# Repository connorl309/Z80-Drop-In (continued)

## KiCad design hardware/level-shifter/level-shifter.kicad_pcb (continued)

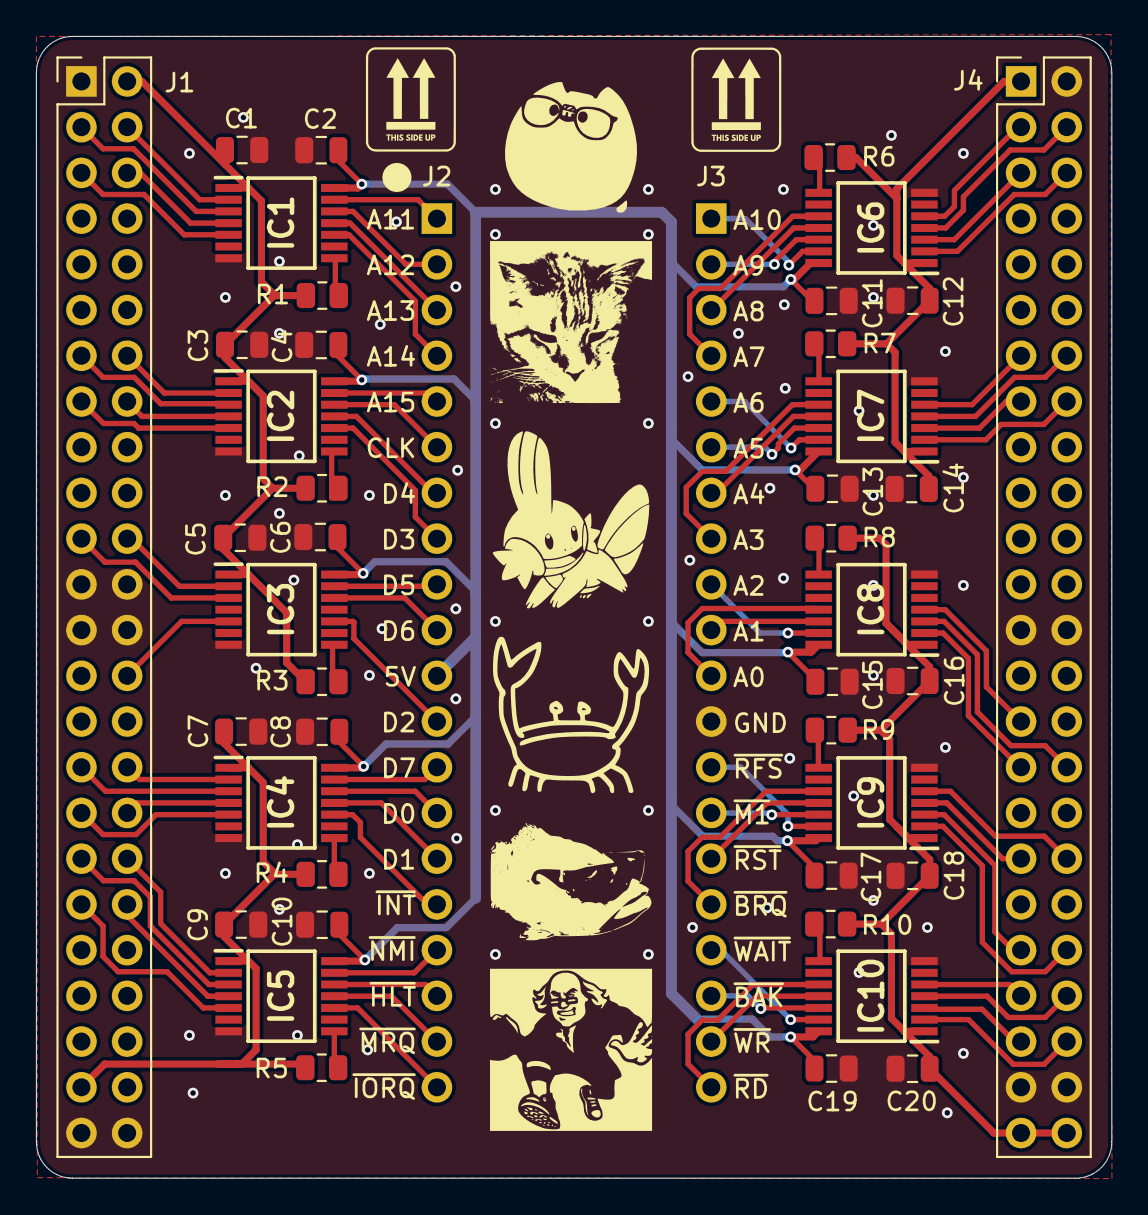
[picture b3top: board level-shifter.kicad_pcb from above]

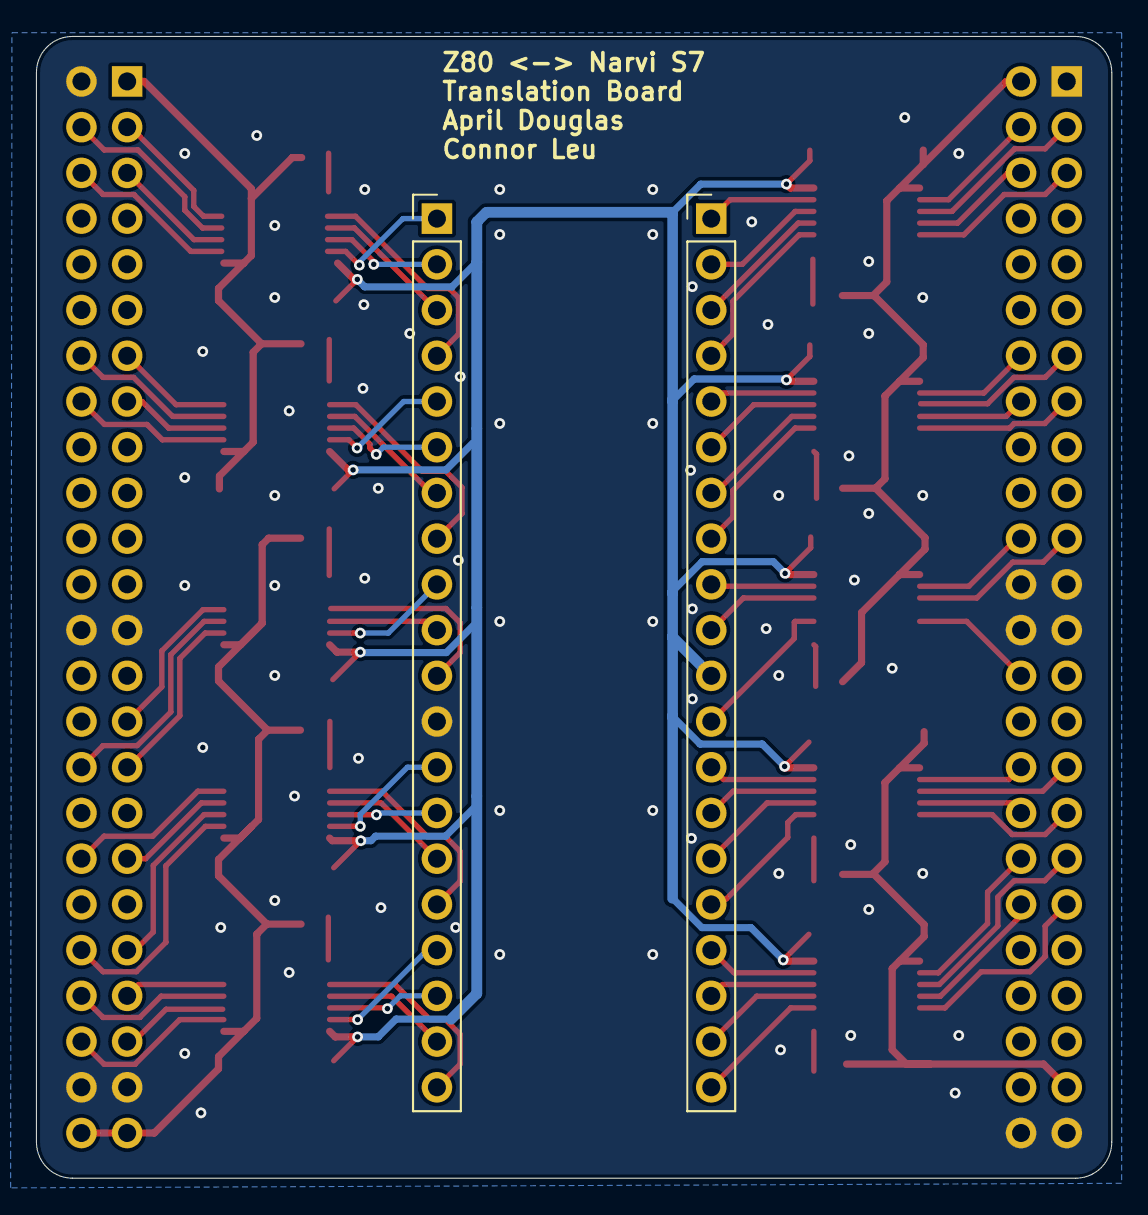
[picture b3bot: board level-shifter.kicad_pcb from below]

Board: 2 copper layers, 59.7 x 63.4 mm, 44 parts (2 on the bottom side), 92 nets.

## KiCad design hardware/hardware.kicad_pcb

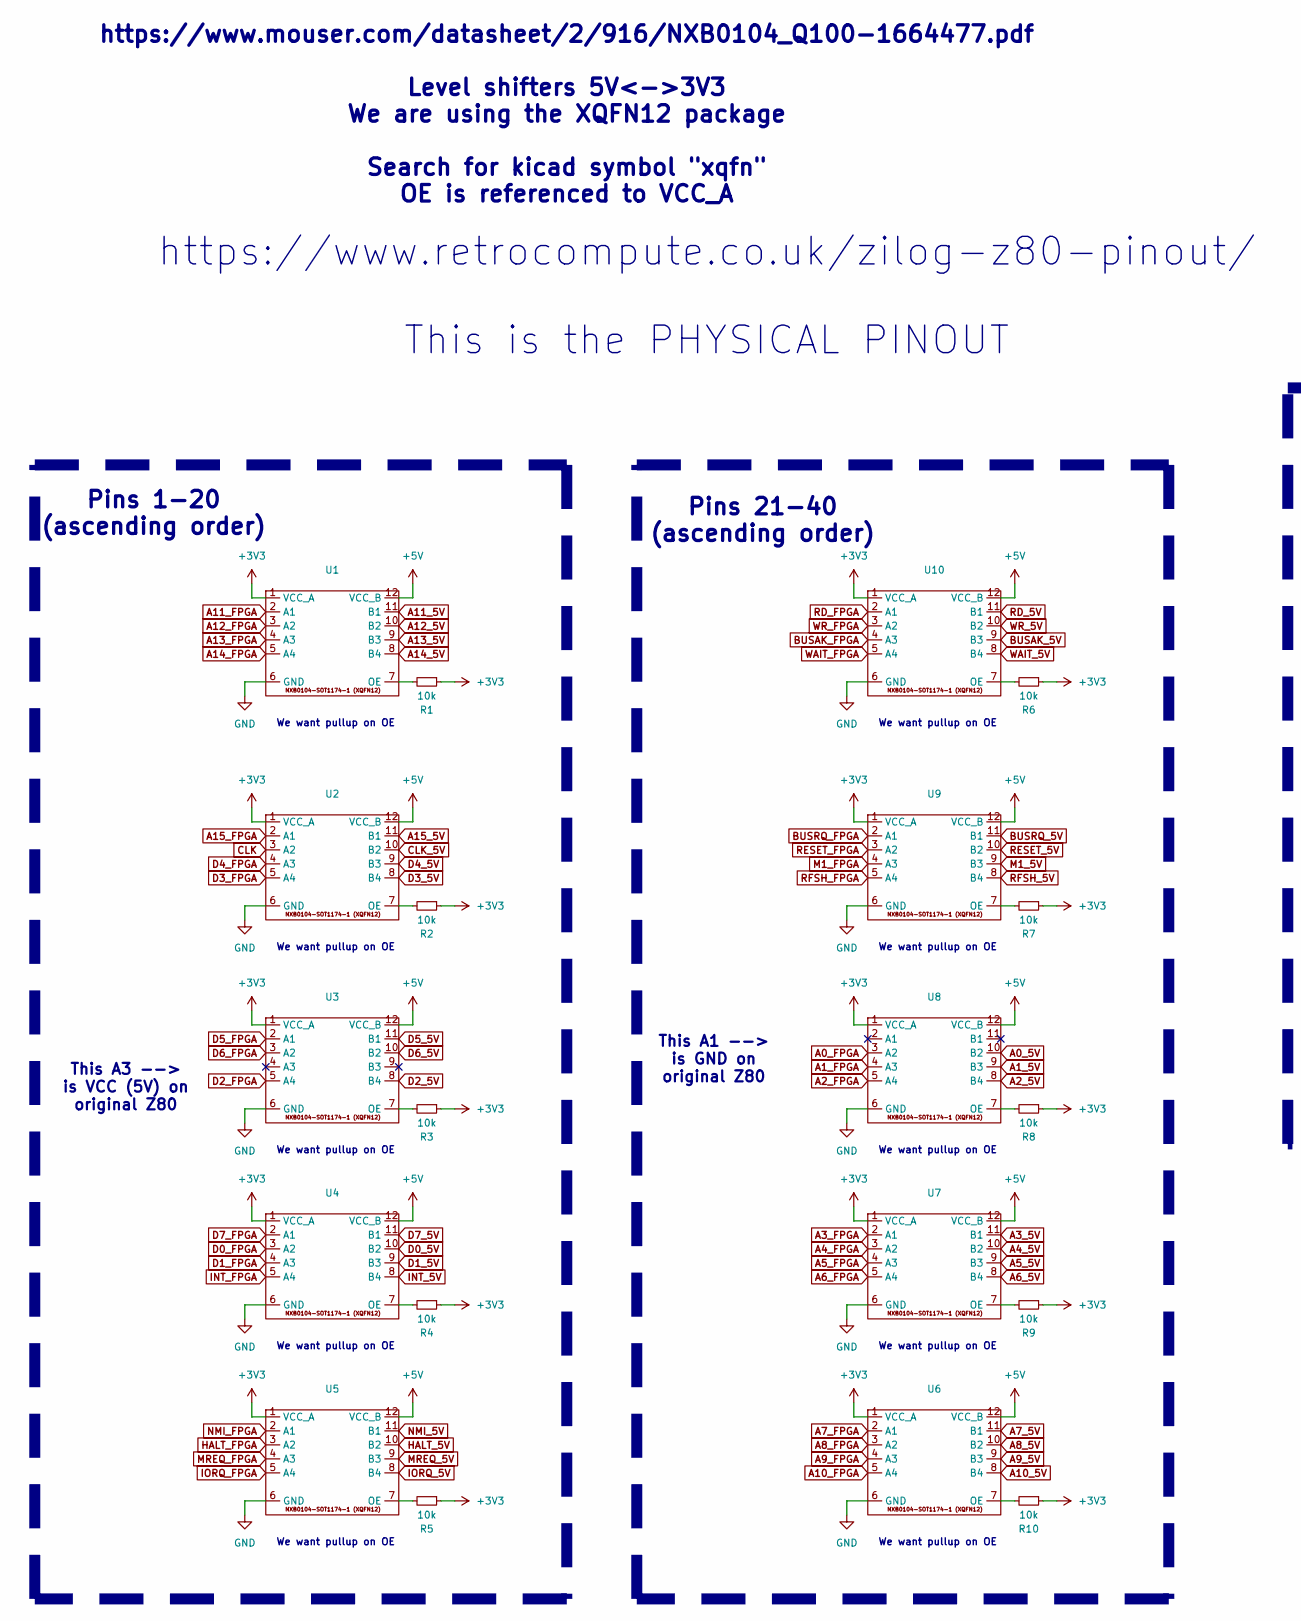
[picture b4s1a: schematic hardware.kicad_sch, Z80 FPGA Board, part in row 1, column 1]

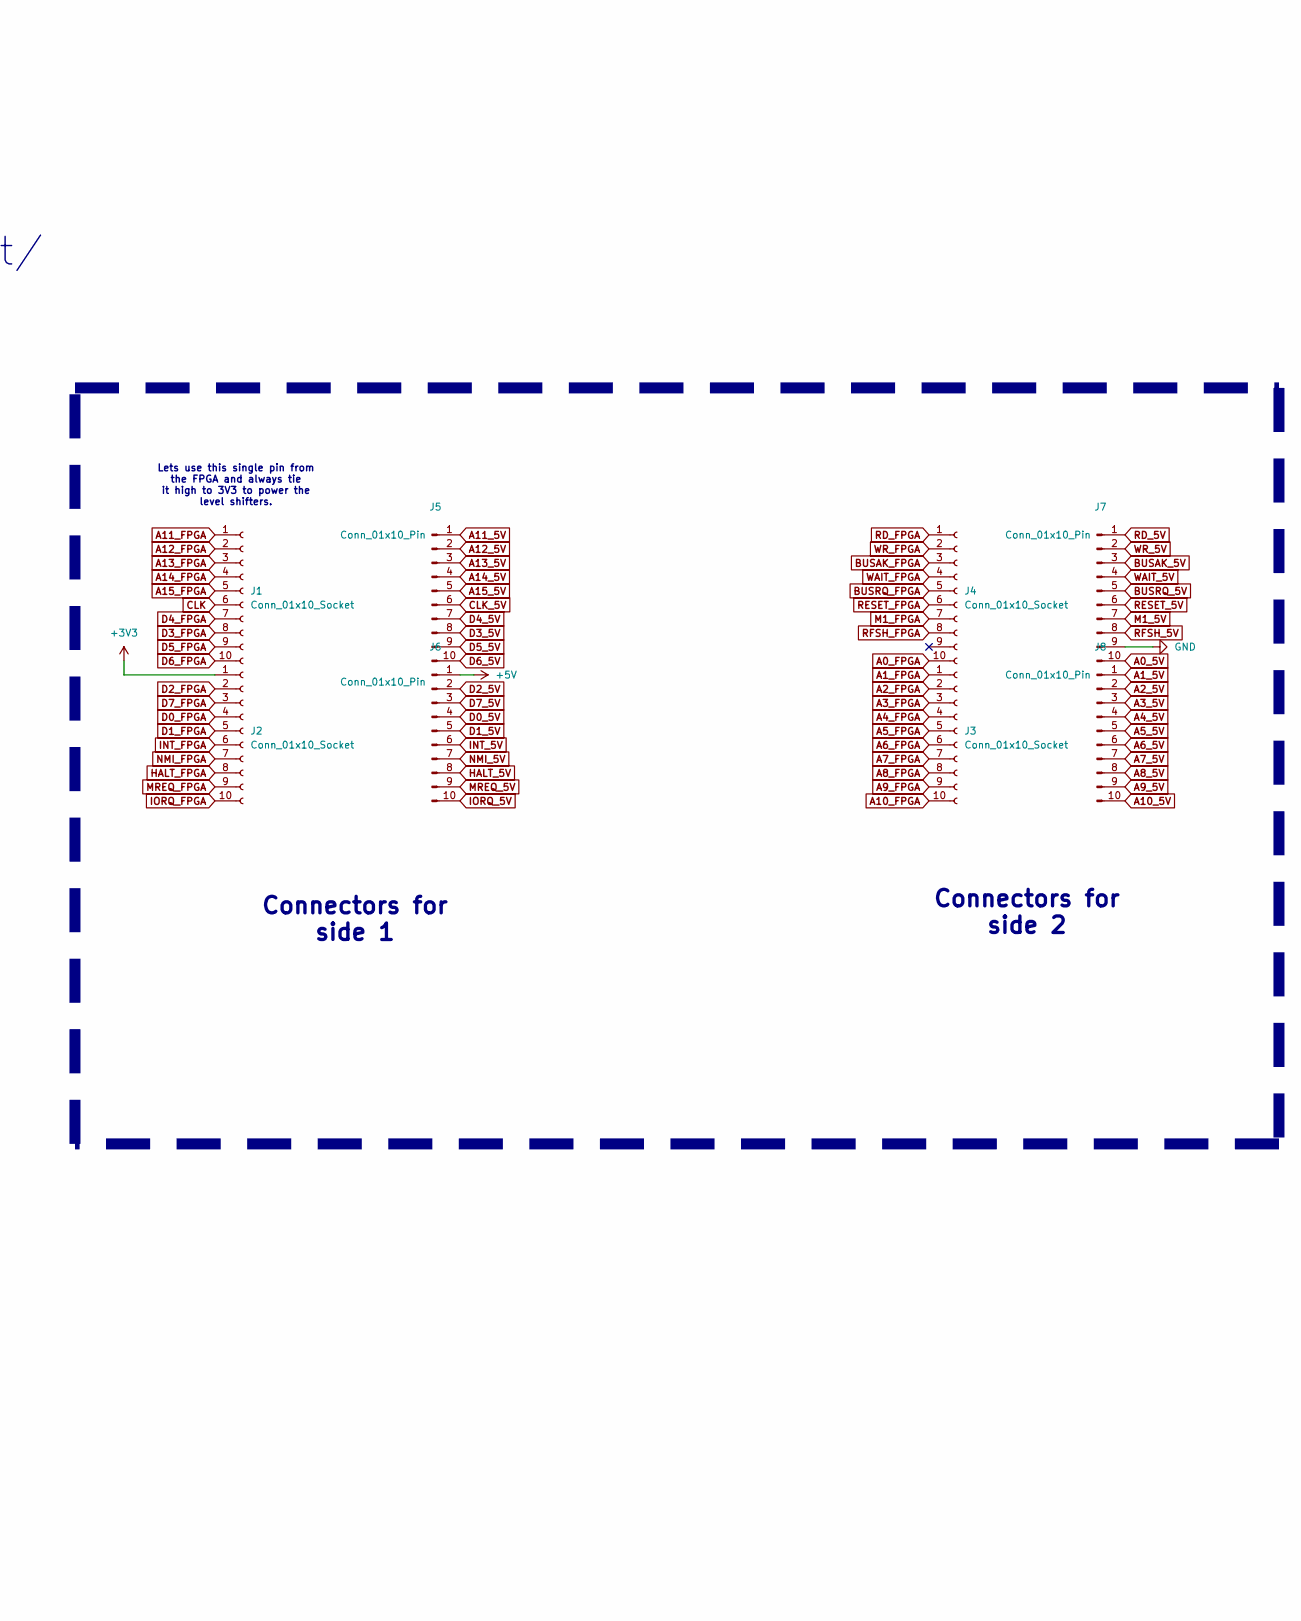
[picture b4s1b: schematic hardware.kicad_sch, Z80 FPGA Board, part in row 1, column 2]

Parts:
J1, J2, J3, J4: Conn_01x10_Socket; PinSocket_1x10_P2.54mm_Vertical
J5, J6, J7, J8: Conn_01x10_Pin; PinHeader_1x10_P2.54mm_Vertical
R1, R2, R3, R4, R5, R6, R7, R8, R9, R10: 10k; R_0201_0603Metric
U1, U2, U3, U4, U5, U6, U7, U8, U9, U10: NXB0104_XQFN12

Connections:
+3V3: J2.1, R1.1, R2.1, R3.1, R4.1, R5.1, R6.1, R7.1, R8.1, R9.1, R10.1, U1.1 (VCC_A), U2.1 (VCC_A), U3.1 (VCC_A), U4.1 (VCC_A), U5.1 (VCC_A), U6.1 (VCC_A), U7.1 (VCC_A), U8.1 (VCC_A), U9.1 (VCC_A), U10.1 (VCC_A)
+5V: J6.1, U1.12 (VCC_B), U2.12 (VCC_B), U3.12 (VCC_B), U4.12 (VCC_B), U5.12 (VCC_B), U6.12 (VCC_B), U7.12 (VCC_B), U8.12 (VCC_B), U9.12 (VCC_B), U10.12 (VCC_B)
A0_5V: J7.10, U8.10 (B2)
A0_FPGA: J4.10, U8.3 (A2)
A1_5V: J8.1, U8.9 (B3)
A1_FPGA: J3.1, U8.4 (A3)
A2_5V: J8.2, U8.8 (B4)
A2_FPGA: J3.2, U8.5 (A4)
A3_5V: J8.3, U7.11 (B1)
A3_FPGA: J3.3, U7.2 (A1)
A4_5V: J8.4, U7.10 (B2)
A4_FPGA: J3.4, U7.3 (A2)
A5_5V: J8.5, U7.9 (B3)
A5_FPGA: J3.5, U7.4 (A3)
A6_5V: J8.6, U7.8 (B4)
A6_FPGA: J3.6, U7.5 (A4)
A7_5V: J8.7, U6.11 (B1)
A7_FPGA: J3.7, U6.2 (A1)
A8_5V: J8.8, U6.10 (B2)
A8_FPGA: J3.8, U6.3 (A2)
A9_5V: J8.9, U6.9 (B3)
A9_FPGA: J3.9, U6.4 (A3)
A10_5V: J8.10, U6.8 (B4)
A10_FPGA: J3.10, U6.5 (A4)
A11_5V: J5.1, U1.11 (B1)
A11_FPGA: J1.1, U1.2 (A1)
A12_5V: J5.2, U1.10 (B2)
A12_FPGA: J1.2, U1.3 (A2)
A13_5V: J5.3, U1.9 (B3)
A13_FPGA: J1.3, U1.4 (A3)
A14_5V: J5.4, U1.8 (B4)
A14_FPGA: J1.4, U1.5 (A4)
A15_5V: J5.5, U2.11 (B1)
A15_FPGA: J1.5, U2.2 (A1)
BUSAK_5V: J7.3, U10.9 (B3)
BUSAK_FPGA: J4.3, U10.4 (A3)
BUSRQ_5V: J7.5, U9.11 (B1)
BUSRQ_FPGA: J4.5, U9.2 (A1)
CLK: J1.6, U2.3 (A2)
CLK_5V: J5.6, U2.10 (B2)
D0_5V: J6.4, U4.10 (B2)
D0_FPGA: J2.4, U4.3 (A2)
D1_5V: J6.5, U4.9 (B3)
D1_FPGA: J2.5, U4.4 (A3)
D2_5V: J6.2, U3.8 (B4)
D2_FPGA: J2.2, U3.5 (A4)
D3_5V: J5.8, U2.8 (B4)
D3_FPGA: J1.8, U2.5 (A4)
D4_5V: J5.7, U2.9 (B3)
D4_FPGA: J1.7, U2.4 (A3)
D5_5V: J5.9, U3.11 (B1)
D5_FPGA: J1.9, U3.2 (A1)
D6_5V: J5.10, U3.10 (B2)
D6_FPGA: J1.10, U3.3 (A2)
D7_5V: J6.3, U4.11 (B1)
D7_FPGA: J2.3, U4.2 (A1)
GND: J7.9, U1.6 (GND), U2.6 (GND), U3.6 (GND), U4.6 (GND), U5.6 (GND), U6.6 (GND), U7.6 (GND), U8.6 (GND), U9.6 (GND), U10.6 (GND)
HALT_5V: J6.8, U5.10 (B2)
HALT_FPGA: J2.8, U5.3 (A2)
INT_5V: J6.6, U4.8 (B4)
INT_FPGA: J2.6, U4.5 (A4)
IORQ_5V: J6.10, U5.8 (B4)
IORQ_FPGA: J2.10, U5.5 (A4)
M1_5V: J7.7, U9.9 (B3)
M1_FPGA: J4.7, U9.4 (A3)
MREQ_5V: J6.9, U5.9 (B3)
MREQ_FPGA: J2.9, U5.4 (A3)
NMI_5V: J6.7, U5.11 (B1)
NMI_FPGA: J2.7, U5.2 (A1)
unnamed: R1.2, U1.7 (OE)
unnamed: R2.2, U2.7 (OE)
unnamed: R3.2, U3.7 (OE)
unnamed: R4.2, U4.7 (OE)
unnamed: R5.2, U5.7 (OE)
unnamed: R10.2, U6.7 (OE)
unnamed: R9.2, U7.7 (OE)
unnamed: R8.2, U8.7 (OE)
unnamed: R7.2, U9.7 (OE)
unnamed: R6.2, U10.7 (OE)
RD_5V: J7.1, U10.11 (B1)
RD_FPGA: J4.1, U10.2 (A1)
RESET_5V: J7.6, U9.10 (B2)
RESET_FPGA: J4.6, U9.3 (A2)
RFSH_5V: J7.8, U9.8 (B4)
RFSH_FPGA: J4.8, U9.5 (A4)
WAIT_5V: J7.4, U10.8 (B4)
WAIT_FPGA: J4.4, U10.5 (A4)
WR_5V: J7.2, U10.10 (B2)
WR_FPGA: J4.2, U10.3 (A2)

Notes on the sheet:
https://www.retrocompute.co.uk/zilog-z80-pinout/ This is the PHYSICAL PINOUT
Connectors for side 1
We want pullup on OE
Pins 21-40 (ascending order)
https://www.mouser.com/datasheet/2/916/NXB0104_Q100-1664477.pdf Level shifters 5V<->3V3 We are using the XQFN12 package Search for kicad symbol "xqfn" OE is referenced to VCC_A
This A3 --> is VCC (5V) on original Z80
Lets use this single pin from the FPGA and always tie it high to 3V3 to power the level shifters.
Connectors for side 2
This A1 --> is GND on original Z80
Pins 1-20 (ascending order)

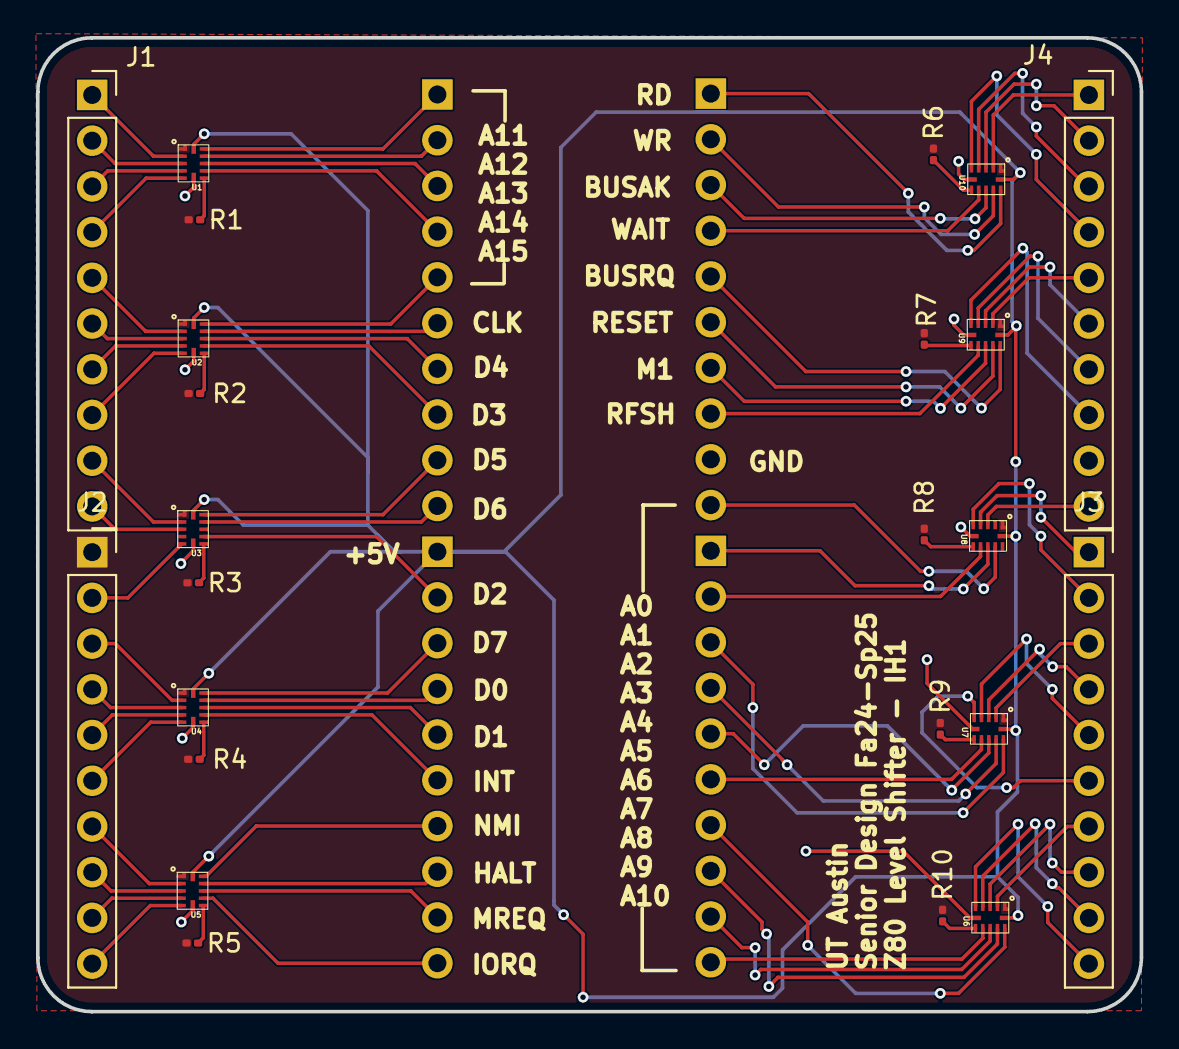
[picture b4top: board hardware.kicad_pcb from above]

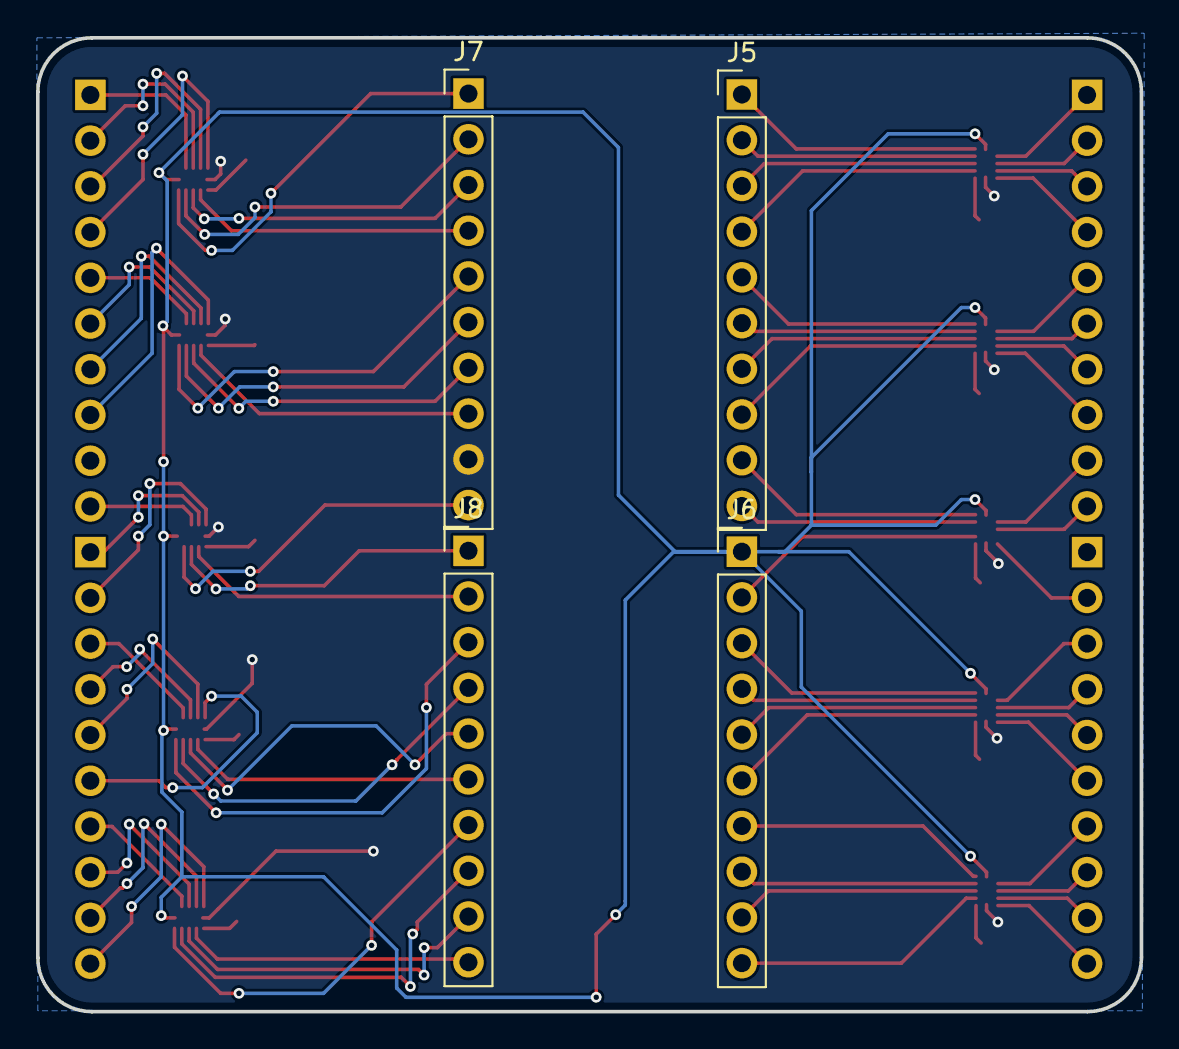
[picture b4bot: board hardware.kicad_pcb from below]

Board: 2 copper layers, 61.3 x 54.1 mm, 28 parts (4 on the bottom side), 89 nets.

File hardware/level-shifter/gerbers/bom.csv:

Designator,Comment,,Footprint,Qty,DNP,LCSC Part Number
"C1,C2",10u,,Capacitor_SMD:C_0805_2012Metric_Pad1.18x1.45mm_HandSolder,2,,C1713
"J1,J2,J3,J4",Conn_01x10_Socket,,Connector_PinHeader_2.54mm:PinHeader_1x10_P2.54mm_Vertical,4,,C57369
"J5,J6,J7,J8",Conn_01x10_Pin,,Connector_PinHeader_2.54mm:PinHeader_1x10_P2.54mm_Vertical,4,,C57369
J9,USB_C_Receptacle_PowerOnly_6P,,Connector_USB:USB_C_Receptacle_GCT_USB4125-xx-x_6P_TopMnt_Horizontal,1,,C2987385
"R1,R2,R3,R4,R5,R6,R7,R8,R9,R10",10k,,Resistor_SMD:R_0805_2012Metric_Pad1.20x1.40mm_HandSolder,10,,C17414
"R11,R12",5k1,,Resistor_SMD:R_0805_2012Metric_Pad1.20x1.40mm_HandSolder,2,,C26023
"U1,U2,U3,U4,U5,U6,U7,U8,U9,U10",~,,hardware:NXB0104_XQFN12,10,,C551618
U11,TLV75533PDBV,,Package_TO_SOT_SMD:SOT-23-5,1,,C404027

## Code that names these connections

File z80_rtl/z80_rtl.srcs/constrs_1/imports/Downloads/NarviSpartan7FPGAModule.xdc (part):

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#                                              QSPI - FLASH                                                        #
####################################################################################################################
#set_property -dict { PACKAGE_PIN "M13"    IOSTANDARD LVCMOS33    SLEW FAST} [get_ports { SPI_CS_N }]     ;              # IO_L6P_T0_FCS_B_14            Sch = SPI_CS_N
#set_property -dict { PACKAGE_PIN "K17"    IOSTANDARD LVCMOS33    SLEW FAST} [get_ports { SPI_DQ[0] }]    ;              # IO_L1P_T0_D00_MOSI_14         Sch = SPI_DQ0
#set_property -dict { PACKAGE_PIN "K18"    IOSTANDARD LVCMOS33    SLEW FAST} [get_ports { SPI_DQ[1] }]    ;              # IO_L1N_T0_D01_DIN_14          Sch = SPI_DQ1
#set_property -dict { PACKAGE_PIN "L14"    IOSTANDARD LVCMOS33    SLEW FAST} [get_ports { SPI_DQ[2] }]    ;              # IO_L2P_T0_D02_14              Sch = SPI_DQ2
#set_property -dict { PACKAGE_PIN "M15"    IOSTANDARD LVCMOS33    SLEW FAST} [get_ports { SPI_DQ[3] }]    ;              # IO_L2N_T0_D03_14              Sch = SPI_DQ3
#set_property -dict { PACKAGE_PIN "C8"     IOSTANDARD LVCMOS33    SLEW FAST} [get_ports { SPI_SCK }]      ;              # CCLK_0                        Sch = SPI_SCK

####################################################################################################################
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
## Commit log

2024-09-06 initial vivado project commit
2024-09-06 Pinout module definition for the chip
2024-09-06 some more boilerplate
2024-09-09 some WIP on Alu
2024-09-10 quick python parse of z80inst.txt
2024-09-10 more parse fixes
2024-09-12 setup kicad proj
2024-09-12 jdafklafkldj
2024-09-22 Added ALU.v, not included in the project file rn tho
2024-09-23 added ALU to project file
2024-09-23 Added more ALU opcodes, still need a few
2024-09-23 finished everything but weird rotates, going to rewrite to use wires
2024-09-23 moving over to wires, looks like I'll need to write a ALU mux module
2024-09-23 Made fully combinational, currently eliminating latches
2024-09-23 Fixed up latches for real this time
2024-09-24 Fixed up Half Carry CC, latches came back :(
2024-09-24 Finished? Doesn't follow undocumented exactly and needs optimizations
2024-09-24 Added Y and X flags
2024-09-24 Added weird ahhh rotates
2024-09-24 Small undocumented effects
2024-09-24 Refactored ALU into submodules and condensed DAA to a SOP
2024-09-24 unrefactored, saved some nets :(
2024-09-24 Added ALU testbench and fixed a bug
2024-09-26 Added comments
2024-10-07 restart hardware proj
2024-10-07 add hardware stuff for symbol/footprint of level shifter
2024-10-07 added z80RegisterFile.v, rough draft
2024-10-09 update level shifter adapter board schematic
2024-10-09 first general schematic/layout pushed. need to look into some stuff
2024-10-09 fix pcb planes
2024-10-10 Added z80RegisterFile.v in \sources_1\new
    Register file with read-write functionality. Need to add latches to dynamically rename registers
2024-10-12 add XC7S15 8x8 BGA footprint and symbol to kicad project
2024-10-12 reorganize some pcb stuff, begin kicad for sip board
2024-10-13 Renamed params to match opcodes and fixed up some undocumented behav
2024-10-14 Added undocumented BIT behavior
2024-10-14 wire up LDOs
2024-10-14 boot config and spi eeprom
2024-10-14 Added flipflops to z80RegisterFile.v
2024-10-14 jtag connector, decoupling caps, level shifters on schematic
2024-10-14 begin layout for sip
    we will need to use pcbway
2024-10-15 fix some connections, layout
2024-10-16 update via settings
2024-10-16 redid part of the board
2024-10-16 castellated hole edges, add 3d model
2024-10-16 pinout labels
2024-10-17 some cleanup
2024-10-17 files
2024-10-18 follow marco stackup
2024-10-18 fixed vivado project XML
2024-10-18 Refactored ALU to use z80_defines and redid current tests
2024-10-18 fixed project file again
2024-10-18 added PASSA and PASSB to ALU
2024-10-18 actually added the tests in this one and added A and F swapping (EX)
2024-10-18 Added LDI/D/IR/DR flag update to ALU.v
2024-10-19 wip layout, part placement
2024-10-19 im actually so fucking goated
2024-10-20 More ALU tests and fixed a couple bugs
2024-10-26 End to end testing on ALU performed, couple of bug fixes
2024-11-01 Revised register file implementation
    .v file in \Z80-Drop-In\z80_rtl\z80_rtl.srcs\sources_1\new
    Full register file dev directory in \Z80-Drop-In\z80_rtl\z80_registerFile
2024-11-04 Added memory module and tests
2024-11-04 Working on more flag instructions
    LD A, I
    LD A, R
    LDI(R)
    LDD(R)
    CPI(R)
    CPD(R)
2024-11-04 finished more complex flag instructions
    IN and OUT
2024-11-04 Changed Register File .v. Also fixed and ran synthesis and implementation for current .v code
    Got rid of tristate buffers on regfile outputs.
    Fixed some more issues with implimentation (mainly some multiply-accessed warnings with the internal regfile bus)
    Kept tristates in front of register decoder and as input to the internal regbus. These can be chagned later but I think the regbus tristate buffer should stay since we will want REG_MUX_OUT to be sep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
2024-11-08 New register file with less control signals and seperate SR/DR signals
2024-11-08 updated register file .v with 8/16 bit reads and a separate bus for concurrent reads of register sets {IX, IY, SP} and general purpose
2024-11-09 "Working" prototype done
    can only run 4 instructions kekw
2024-11-09 Switched memory to block RAM IP
2024-11-11 decode header
2024-11-11 Simplified register file design. Fleshed out testbench in register file. Fixed bug with double register writes
2024-12-06 Finish draft 1(.5?) of SiP board. Needs to be looked at again and probably redone.
2025-01-14 fix the git branch bc it was broken??
2025-01-14 add new spi chip supported by vivado
2025-01-14 3d model for fpga, part placement done(?)
    Look into Xilinx programming adapters still. We do not have lots of space to work with.
2025-01-15 update to use relative paths
2025-01-15 fix the paths (again)
2025-01-16 add new parts: button, jtag connector
2025-01-16 placement done, new dip switch
    need to start picking parts and routing
2025-01-16 text
2025-01-16 stop routing need to change schematic (again)
2025-01-16 raahhhhh my eyeballs hurt
2025-01-18 non-gpio routing done for "v3" (really like v6)
2025-01-18 remove all but 3v3 LED
    not enough voltage/current from the other 2 power rails to light up an LED
2025-01-19 merging stuff
2025-01-21 Some fixes I don't remember
2025-01-23 no m-state designations
2025-01-23 init testing psh. dont use
2025-01-24 Logging example that works on Narvi board
2025-01-24 Made proof of concept block design datapath and adding logging
2025-01-24 Update gitignore
2025-01-24 push
2025-01-26 UART and ILA goodness
2025-01-27 idk lol:
2025-01-27 pushign stuff
2025-01-27 Add usequencer.v (finally :D)
2025-01-27 ocmmit2
2025-01-28 level shifter redo
2025-01-28 pushing again
2025-01-28 Fixed xpr file
2025-01-28 remove old files from level shifter proj, add MPN for macrofab possible assembly
2025-01-28 use marco USB header and filtering, add MPNs, via stitching for power planes
2025-01-30 readme - more project info, testing
2025-01-30 remove python testing stuff from branch; april uart/ila will be used instead
2025-01-30 WE REDOIN PCB
2025-01-30 merg
2025-01-30 I hate everything
2025-01-30 Funny slicer and ALU no longer has AF registers
2025-01-30 applied requested changes to datapath, waiting on register file rework
2025-01-30 redo layout of sip (again), changed switching reg to be on surface, need to route, need to add 2 more layers for 5V plane
2025-01-30 Fix GATE_ macro capitalisation in fsm.v
2025-01-30 work on layout (im sad)
2025-01-31 add gnd stitching vias. buried.
2025-02-02 start of devhat redo
    remove usb stuff because the devboard supplies 3.3v
    pinout of devboard was wackier than previously thought
2025-02-02 devhat redo "done"
    NO PEEKING AT THE BOARD UNTIL THE REVEAL!!!
2025-02-02 changed constraints to match oshpark
2025-02-02 sending off for review
2025-02-02 Fix M-cycle state numbers
2025-02-02 Set LAST_T in T-states missing it
2025-02-02 Set COND0 in T-states missing it
2025-02-03 Remove dummy state machine from usequencer.
2025-02-03 Merge register file with rest of RTL
    Added tb_registerfile testbench, z80RegisterFile.v source, and changed name of April's proof-of-concept one to z80RegisterFile_April.
    Also deleted my old register file project that was in main.
2025-02-03 added decoupling caps to level shifters
2025-02-04 updated DRC to match MacroFab
2025-02-04 Off for review (again)
2025-02-05 prep for redo switching regulator sip
2025-02-06 wip vreg
2025-02-08 sip vreg redo, connect level shifters to outside pins
2025-02-09 New Version of Regfile compatible with control block
2025-02-11 routed to level shifters, need to address DRC
2025-02-16 Made progress on wiring up the datapath
    Changes need to be made because there is some hairbrained stuff going on
2025-02-17 weeee
2025-02-17 Revised register file :p
    Revised EXX functionality, cleaned up floating ports, simplified register reads, fixed some bad no-no verilog.
2025-02-17 Test assembly programs for z80 instructions
2025-02-24 flag exchange
2025-02-24 yay I forgot stuff
2025-02-26 Fix bug with external control signals set on rising edge
2025-02-26 Add IFF1 and IFF2 to usequencer
2025-02-26 Fix syntax error in IFF handling (I committed too soon. :P)
2025-02-26 Fix NMI to be active low in decode
2025-02-27 Add support for prefixed instructions
2025-03-03 Rest of instructions (i think unless I missed some undocumnted ones)
2025-03-06 wip test generator/parser
2025-03-09 Small regfile tweaks for synthesis
2025-03-09 quick adjustment for DRC
2025-03-10 Level Shifter Board Testing Code
2025-03-10 Z80 can go through a basic program
    00111110 // ADD A, 100 [LOOP]
    01100100 // 100
    00000110 // ADD B, -1
    11111111 // -1
    10000000 // ADD A, B
    11000010 // JP NZ Loop
2025-03-19 move silkscreen around
2025-03-21 Revised regsiter file again
    Added reset
2025-03-31 setup kicad for breakout board
2025-04-07 untested code that might not work
2025-04-11 Go nuts!
2025-04-13 IT SYNTHESIZES!!!!
2025-04-13 Please help Vivado hates me
2025-04-13 Okay, please work with me Vivado
2025-04-14 Fixed register file synthesis problem (hopefully)
2025-04-18 dont trust this, im just pushing what's on my puter
